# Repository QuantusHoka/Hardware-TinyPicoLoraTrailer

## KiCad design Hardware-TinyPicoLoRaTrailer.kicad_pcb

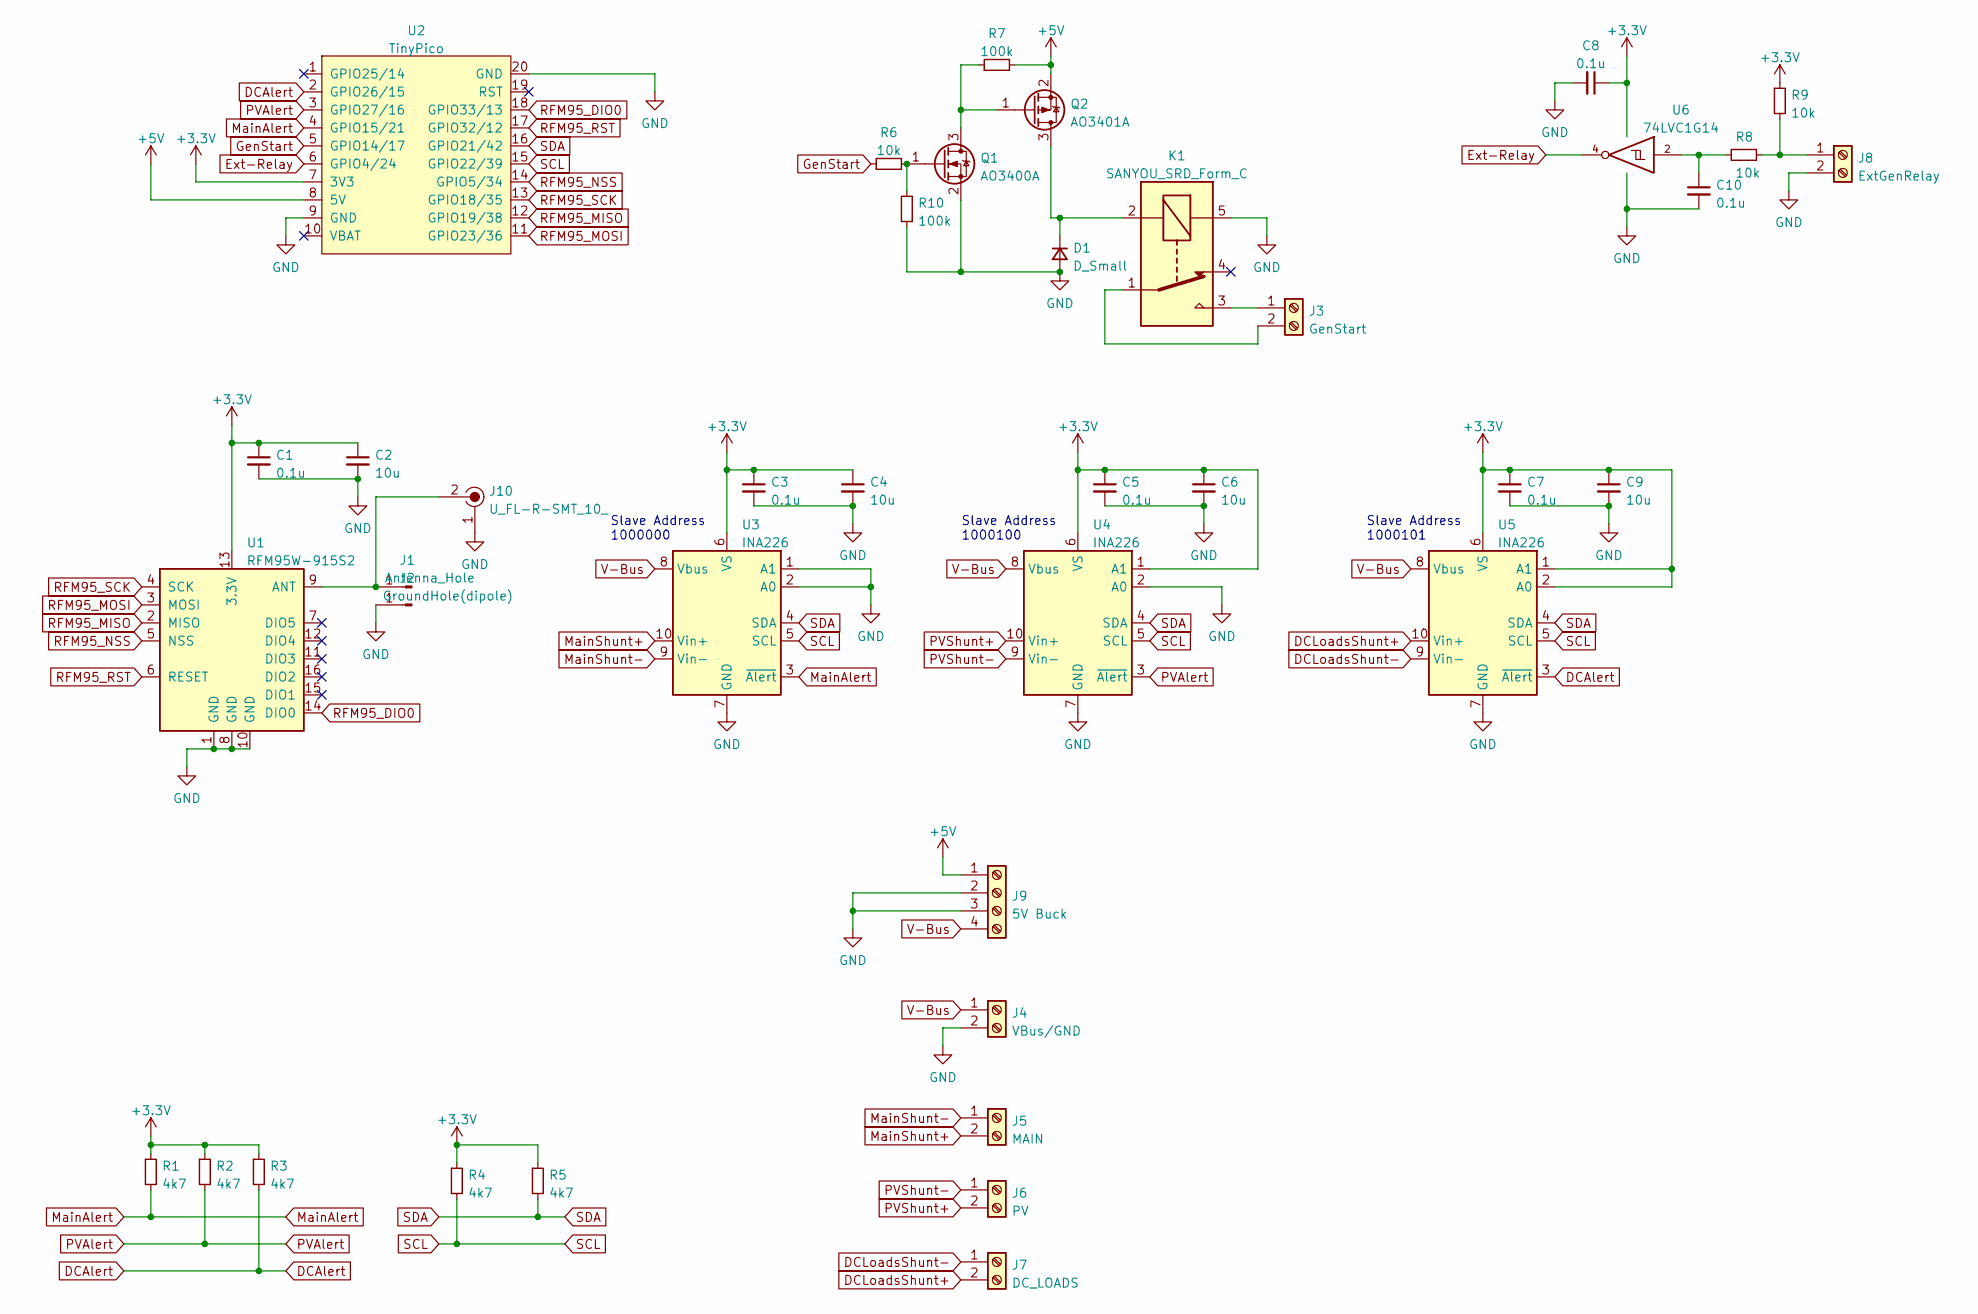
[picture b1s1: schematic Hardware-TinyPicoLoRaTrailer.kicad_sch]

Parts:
C1, C3, C5, C7, C8, C10: 0.1u; C_1206_3216Metric_Pad1.33x1.80mm_HandSolder; LCSC Part Number C82601
C2, C4, C6, C9: 10u; CP_EIA-3216-18_Kemet-A_Pad1.58x1.35mm_HandSolder; LCSC Part Number C7171
D1: D_Small; D_SMA_Handsoldering; LCSC Part Number C95872
J1: Antenna_Hole; PinHeader_1x01_P1.27mm_Vertical
J2: GroundHole(dipole); PinHeader_1x01_P1.27mm_Vertical
J3: GenStart; TerminalBlock_Phoenix_MKDS-1,5-2-5.08_1x02_P5.08mm_Horizont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
J4: VBus/GND; TerminalBlock_Phoenix_MKDS-1,5-2-5.08_1x02_P5.08mm_Horizont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
J5: MAIN; TerminalBlock_Phoenix_MKDS-1,5-2-5.08_1x02_P5.08mm_Horizont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
J6: PV; TerminalBlock_Phoenix_MKDS-1,5-2-5.08_1x02_P5.08mm_Horizont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
J7: DC_LOADS; TerminalBlock_Phoenix_MKDS-1,5-2-5.08_1x02_P5.08mm_Horizont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
J8: ExtGenRelay; TerminalBlock_Phoenix_MKDS-1,5-2-5.08_1x02_P5.08mm_Horizont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
J9: 5V Buck; TerminalBlock_Phoenix_MKDS-1,5-4-5.08_1x04_P5.08mm_Horizont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
J10: U_FL-R-SMT_10_; Coax_Conn_U.FL; MPN U.FL-R-SMT(10); Digi-Key_PN H9161CT-ND
K1: SANYOU_SRD_Form_C; Relay_SPDT_SANYOU_SRD_Series_Form_C
Q1: AO3400A; SOT-23; LCSC Part Number C20917
Q2: AO3401A; SOT-23; LCSC Part Number C15127
R1, R2, R3, R4, R5: 4k7; R_1206_3216Metric_Pad1.30x1.75mm_HandSolder; LCSC Part Number C17936
R6, R8, R9: 10k; R_1206_3216Metric_Pad1.30x1.75mm_HandSolder; LCSC Part Number C17902
R7, R10: 100k; R_1206_3216Metric_Pad1.30x1.75mm_HandSolder; LCSC Part Number C17900
U1: RFM95W-915S2; HOPERF_RFM9XW_SMD
U2: TinyPico
U3, U4, U5: INA226; VSSOP-10_3x3mm_P0.5mm; LCSC Part Number C49851
U6: 74LVC1G14; SOT-23-5_HandSoldering

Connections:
+3.3V: C1.1, C2.1, C3.1, C4.1, C5.1, C6.1, C7.1, C8.1, C9.1, R1.1, R2.1, R3.1, R4.1, R5.1, R9.1, U1.13 (3.3V), U2.7 (3V3), U3.6 (VS), U4.1 (A1), U4.6 (VS), U5.1 (A1), U5.2 (A0), U5.6 (VS), U6.5 (VCC)
+5V: J9.1, Q2.2 (S), R7.2, U2.8 (5V)
DCAlert: R3.2, U2.2 (GPIO26/15), U5.3 (~Alert)
DCLoadsShunt+: J7.2, U5.10 (Vin+)
DCLoadsShunt-: J7.1, U5.9 (Vin-)
Ext-Relay: U2.6 (GPIO4/24), U6.4
GND: C1.2, C2.2, C3.2, C4.2, C5.2, C6.2, C7.2, C8.2, C9.2, C10.2, D1.2 (A), J2.1, J4.2, J8.2, J9.2, J9.3, J10.1, K1.5, Q1.2 (S), R10.1, U1.1 (GND), U1.8 (GND), U1.10 (GND), U2.9 (GND), U2.20 (GND), U3.1 (A1), U3.2 (A0), U3.7 (GND), U4.2 (A0), U4.7 (GND), U5.7 (GND), U6.3 (GND)
GenStart: R6.1, U2.5 (GPIO14/17)
MainAlert: R1.2, U2.4 (GPIO15/21), U3.3 (~Alert)
MainShunt+: J5.2, U3.10 (Vin+)
MainShunt-: J5.1, U3.9 (Vin-)
unnamed: C10.1, R8.2, U6.2
unnamed: D1.1 (K), K1.2, Q2.3 (D)
unnamed: J1.1, J10.2, U1.9 (ANT)
unnamed: J3.1, K1.3
unnamed: J3.2, K1.1
unnamed: J8.1, R8.1, R9.2
unnamed: Q1.1 (G), R6.2, R10.2
unnamed: Q1.3 (D), Q2.1 (G), R7.1
PVAlert: R2.2, U2.3 (GPIO27/16), U4.3 (~Alert)
PVShunt+: J6.2, U4.10 (Vin+)
PVShunt-: J6.1, U4.9 (Vin-)
RFM95_DIO0: U1.14 (DIO0), U2.18 (GPIO33/13)
RFM95_MISO: U1.2 (MISO), U2.12 (GPIO19/38)
RFM95_MOSI: U1.3 (MOSI), U2.11 (GPIO23/36)
RFM95_NSS: U1.5 (NSS), U2.14 (GPIO5/34)
RFM95_RST: U1.6 (RESET), U2.17 (GPIO32/12)
RFM95_SCK: U1.4 (SCK), U2.13 (GPIO18/35)
SCL: R4.2, U2.15 (GPIO22/39), U3.5 (SCL), U4.5 (SCL), U5.5 (SCL)
SDA: R5.2, U2.16 (GPIO21/42), U3.4 (SDA), U4.4 (SDA), U5.4 (SDA)
V-Bus: J4.1, J9.4, U3.8 (Vbus), U4.8 (Vbus), U5.8 (Vbus)

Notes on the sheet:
Slave Address 1000101
Slave Address 1000000
Slave Address 1000100

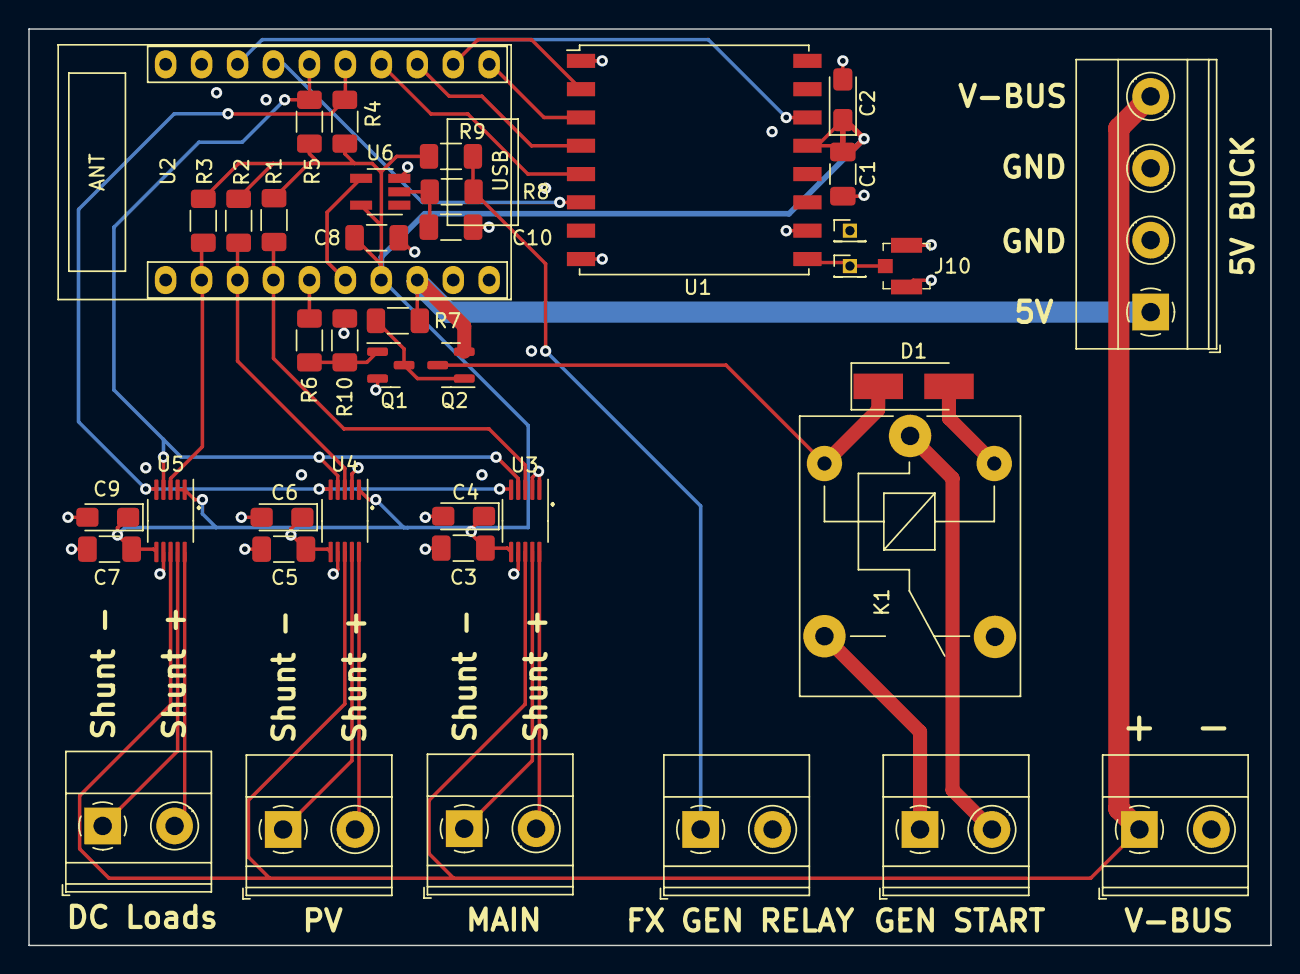
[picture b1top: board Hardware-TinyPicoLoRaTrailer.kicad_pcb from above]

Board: 4 copper layers, 87.8 x 64.8 mm, 40 parts (0 on the bottom side), 31 nets.

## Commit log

2023-01-26 Update 2023-01-25
